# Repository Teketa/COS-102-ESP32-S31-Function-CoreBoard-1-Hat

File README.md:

# COS-102 hat for ESP32-S31-Function-CoreBoard-1

KiCad project for a hat that plugs onto the CoreBoard's J2 header and drives the
Delta COS-102 LED sign's IDC "IN" connector. It is built from `SCHEMATIC.md`, with
the GPIO map changed for the S31 board.

Files: `cos102_s31_hat.kicad_pro` / `.kicad_sch` / `.kicad_pcb`, plus a project
symbol library (`cos102_hat.kicad_sym`, the CoreBoard J2 symbol with real pin
names) and footprint library (`cos102_hat.pretty`, the button access hole).
Saved in KiCad 7 format, so KiCad 7, 8, 9 and 10 all open it (newer versions
upgrade it on save).

## GPIO map: firmware must change

The ESP32-S3 pins in `pins.h` (4-8, 15-18) are not on the S31 board's J2,
except GPIO4, and GPIO4 is also the Ethernet PHY interrupt (`ETH_INTN`, through
R83). The hat uses nine free pins next to each other on J2:

```c
#define PIN_CLK    47   // J2.13 -> U8A  -> R1  -> P1.10
#define PIN_R      48   // J2.14 -> U8D  -> R4  -> P1.4   (+ U10B -> R10 -> P1.1 copy)
#define PIN_G      45   // J2.15 -> U8C  -> R3  -> P1.3
#define PIN_B      46   // J2.16 -> U8B  -> R2  -> P1.2
#define PIN_LAT    43   // J2.17 -> U9A  -> R5  -> P1.9
#define PIN_GCLK   44   // J2.18 -> U9B  -> R6  -> P1.11
#define PIN_ADDR_A 40   // J2.19 -> U9C  -> R7  -> P1.8
#define PIN_ADDR_B 42   // J2.20 -> U9D  -> R8  -> P1.7
#define PIN_ADDR_C 39   // J2.21 -> U10A -> R9  -> P1.6
```

CLK and the three data lines share U8, as in `SCHEMATIC.md`.

Pins deliberately avoided, from the CoreBoard schematic and the ESP32-S31 IO guide:

| GPIO | Why |
|---|---|
| 4 | Also wired to the Ethernet PHY interrupt (ETH_INTN) through 0 Ohm R83 |
| 36, 37 | Strapping (VDD_SPI voltage, JTAG select) |
| 60 | Strapping + on-board RGB LED |
| 61 | Strapping (BOOT) + BOOT button |
| 58, 59 | UART0 to the CP2102N (console, `oc fast` etc.) |

Spare and free on J2: GPIO0-3, 20-25 (SD pins), 35, 38, 49.

## Power

Same as `SCHEMATIC.md`: J1 (display PSU 5 V) -> F1 2 A slow -> D1 TVS / C5 ->
FB1+FB2 -> L1 47 uH + C6 1000 uF -> FB3 -> buffers, and -> D2 SS34 -> C8 470 uF
-> CoreBoard 5V pins (J2.39/40).

On the CoreBoard, the 5V header pins are `VCC_5V`, the output of the LM66200
ideal-diode OR of both USB-C ports. That rail also feeds the 3.3 V buck, the
USB-A host switch (up to 500 mA) and the speaker amp. D2 stops the board's USB
from powering the panel. USB can stay plugged in for flashing.

GND_IN (J1 pin 2, D1, C5, FB2 pin 1) has its own copper island on the top layer
(`GND_IN_island` zone). The main GND pours on both layers start after FB2.

## Mechanics

- 65 x 55 mm, same outline as the CoreBoard. 3.5 mm corner radius, 4x M2.5 holes on the board's 58 x 48 mm grid.
- J2 is a 2x20 female socket (8.5 mm body) on the BOTTOM side. Every pad was
  checked against the CoreBoard header positions from Espressif's DXF; pin 1 is
  on the inner row at the left end.
- Stack height: 2.54 mm header plastic + 8.5 mm socket = 11 mm. Use M2.5 x 11 mm standoffs.
- Cut-out over the RJ45 (x >= 43.5 mm, y 17-44.5 mm). The CoreBoard's USB-A is
  a side-mount part standing on edge, so both are taller than 11 mm.
- 3.2 mm holes over the BOOT and RST buttons, so you can press them with a toothpick.
- Copper keep-out (both layers) along the left edge, where the module's PCB antenna hangs off the CoreBoard.
- `User.Drawings` shows the CoreBoard RJ45, USB-A and module outline for reference.

## Check before ordering

1. **P1 pin 1** against the ribbon's triangle mark (unchanged from `SCHEMATIC.md`).
2. **IDC pins 5, 13, 15** are left unconnected until they have been metered.
3. Panel 5 V current. Bench test with a current-limited supply first.

Already checked: ERC is clean (0 errors, 0 warnings) in your KiCad. The board
has no courtyard overlaps. J1's wire openings face the bottom board edge
(checked against its 3D model). J1 stands about 13.8 mm tall above the hat.

## Layout and routing

P1 (the ribbon to the panel) sits on the bottom edge next to J1, so both cables
plug in along the same edge. Pin 1 is at the left, in the same orientation as
before. The fuse F1 sits in the gap between P1 and J1. The input TVS/bypass/beads
(D1, C5, FB1, FB2) sit just above them. L1 and C6 are in the middle of the board.

The board is routed on 2 layers. Most tracks are on top. The bottom is a GND
plane, cut only by about 176 mm of short jumpers.

- 68 vias. Each buffer has a GND bus under its body that joins pins 1/4/7/10/13,
  with two vias to the plane. Each decoupling cap is tied straight to pins 13/14.
  Every other SMD GND pad has its own via.
- GND_IN (J1 pin 2, D1, C5, FB2 pin 1) is its own short 0.8 mm track and never touches the plane.
- Track widths: Power 0.8 mm, +5V_BUF 0.5 mm, panel side 0.3 mm, 3.3 V side 0.25 mm.
- Clock/data path lengths from J2 to P1: CLK 60 mm, G 53 mm, B 65 mm, R 74 mm
  (R includes the pin-1 copy branch). That's under 0.1 ns of skew, negligible at 18 MHz.
- DRC (zones filled): 0 unconnected, 0 clearance errors at 0.2 mm for signals and
  0.25 mm for power/GND. Left over: library silkscreen lines (P1's pin-1 marker,
  J1's front edge) that run past the board edge and get trimmed.

It was autorouted with a small grid router, because Freerouting isn't installed
here. Press B after any edit to refill the zones.

## JLCPCB (standard 2-layer, 1 oz) check

| Rule | JLCPCB minimum | This board |
|---|---|---|
| Track width / spacing | 0.10 / 0.10 mm | 0.25 / 0.20 mm |
| Via hole / diameter | 0.15 / 0.25 mm | 0.30 / 0.60 mm (power 0.40 / 0.80) |
| PTH annular ring | 0.18 mm (0.25 recommended) | 0.35 mm |
| Hole to hole, vias | 0.20 mm | 0.61 mm |
| Hole to hole, via to pad | 0.45 mm | 0.75 mm |
| Pad to pad | 0.15 mm | 0.20 mm |
| PTH hole to track | 0.28 mm | 0.55 mm |
| NPTH to copper | 0.20 mm | 0.25 mm |
| Copper to board edge | 0.20 mm | 0.50 mm |
| Solder mask bridge | 0.10 mm (green) | 0.67 mm (SOIC-14 pins) |
| Min NPTH | 0.50 mm | 3.2 mm |
| Silkscreen text height | 1.0 mm | 1.0 mm |
| Silkscreen line width | 0.15 mm | 0.12 mm in KiCad library footprints* |

\* KiCad's standard library footprints draw silkscreen outlines at 0.12 mm.
JLCPCB prints them, though possibly thinner or with small gaps. This is cosmetic
only and doesn't affect fabrication.

For JLCPCB assembly you would also need LCSC part numbers in the BOM. The
footprints are all standard. J1, P1, J2, C6 and C8 are through-hole parts, so
solder them by hand (or pay for THT assembly).

## BOM (JLCPCB / LCSC, checked against the JLCPCB catalogue of 2026-11-05)

`jlcpcb_bom.csv` is ready to upload to JLCPCB assembly. Every symbol and footprint also
carries an `LCSC` field, so the KiCad JLCPCB plugins pick the numbers up as well.

| Ref | Part | LCSC | Type | Stock | Price (1+) |
|---|---|---|---|---|---|
| U8, U9, U10 | TI SN74AHCT125DR, SOIC-14 | C155176 | Extended | 2,513 | $0.40 |
| R1-R10 | UNI-ROYAL 0603WAF330JT5E, 33 R 1 % 0603 | C23140 | Basic | 5.07 M | $0.0025 |
| C1-C3, C5, C7, C9 | YAGEO CC0603KRX7R9BB104, 100 nF 50 V X7R | C14663 | Basic | 50 M | $0.014 |
| C4 | Samsung CL21A106KAYNNNE, 10 uF 25 V X5R 0805 | C15850 | Basic | 3.7 M | $0.069 |
| L1 | Bourns SRR1260-470M, 47 uH, Isat 2.6 A, 86 mOhm | C1329363 | Extended | 600 | $1.48 |
| FB1, FB2 | Murata BLM31PG121SN1L, 1206, 3.5 A, 20 mOhm | C85841 | Extended | 49,437 | $0.16 |
| FB3 | Murata BLM18PG221SN1D, 0603, 1.4 A | C80165 | Extended | 298,012 | $0.015 |
| F1 | Littelfuse 0452002.MRL, 2 A slow-blow | C142852 | Extended | 12,284 | $0.33 |
| D1 | MDD SMBJ5.0A, unidirectional TVS | C113974 | Extended | 178,091 | $0.059 |
| D2 | MDD SS34, SMA | C8678 | Basic | 4.0 M | $0.035 |
| C6 (THT) | Rubycon 16YXF1000MEFC10X20, 1000 uF 16 V, 10x20, 78 mOhm | C110138 | Extended | 6,499 | $0.20 |
| C8 (THT) | Nichicon UHE1A471MPD1TD, 470 uF 10 V, 8 mm | C1579341 | Extended | 1,489 | $0.14 |
| J1 (THT) | Phoenix Contact 1729128 (MKDS 1,5/2-5,08) | C7509570 | Extended | 1,306 | $0.54 |
| P1 (THT) | XFCN BH254V-16P, 2x8 box header | C492443 | Extended | 114,323 | $0.16 |
| J2 (THT, bottom) | CONNFLY DS1023-2*20SF11, 2x20 female, 8.5 mm | C132132 | Extended | 2,884 | $0.49 |
| H1-H4 | M2.5 mounting holes, no part | | | | |

- SMT parts cost about $3.60 per board. Six SMT parts are Extended (U, L1, FB1/2, FB3, F1, D1),
  which adds about $18 in setup fees per order ($3 per unique Extended part).
  None of them has a Basic equivalent in the catalogue.
- The through-hole parts (C6, C8, J1, P1, J2) cost about $1.50. Solder them by hand, or
  pay for JLCPCB's THT assembly. J2 goes on the bottom side.
- Lowest stock is L1 (600). Stock moves, so re-check before ordering.
- Cheaper J1 alternative: KF128-5.08-2P-AA (C474952, $0.19, 62k in stock), same 5.08 mm
  pitch. Check its pin and body against the MKDS footprint before swapping.
- The parts file (CPL) and Gerbers are best produced with the JLCPCB fabrication
  plugin in KiCad, which applies JLCPCB's rotation offsets per footprint.

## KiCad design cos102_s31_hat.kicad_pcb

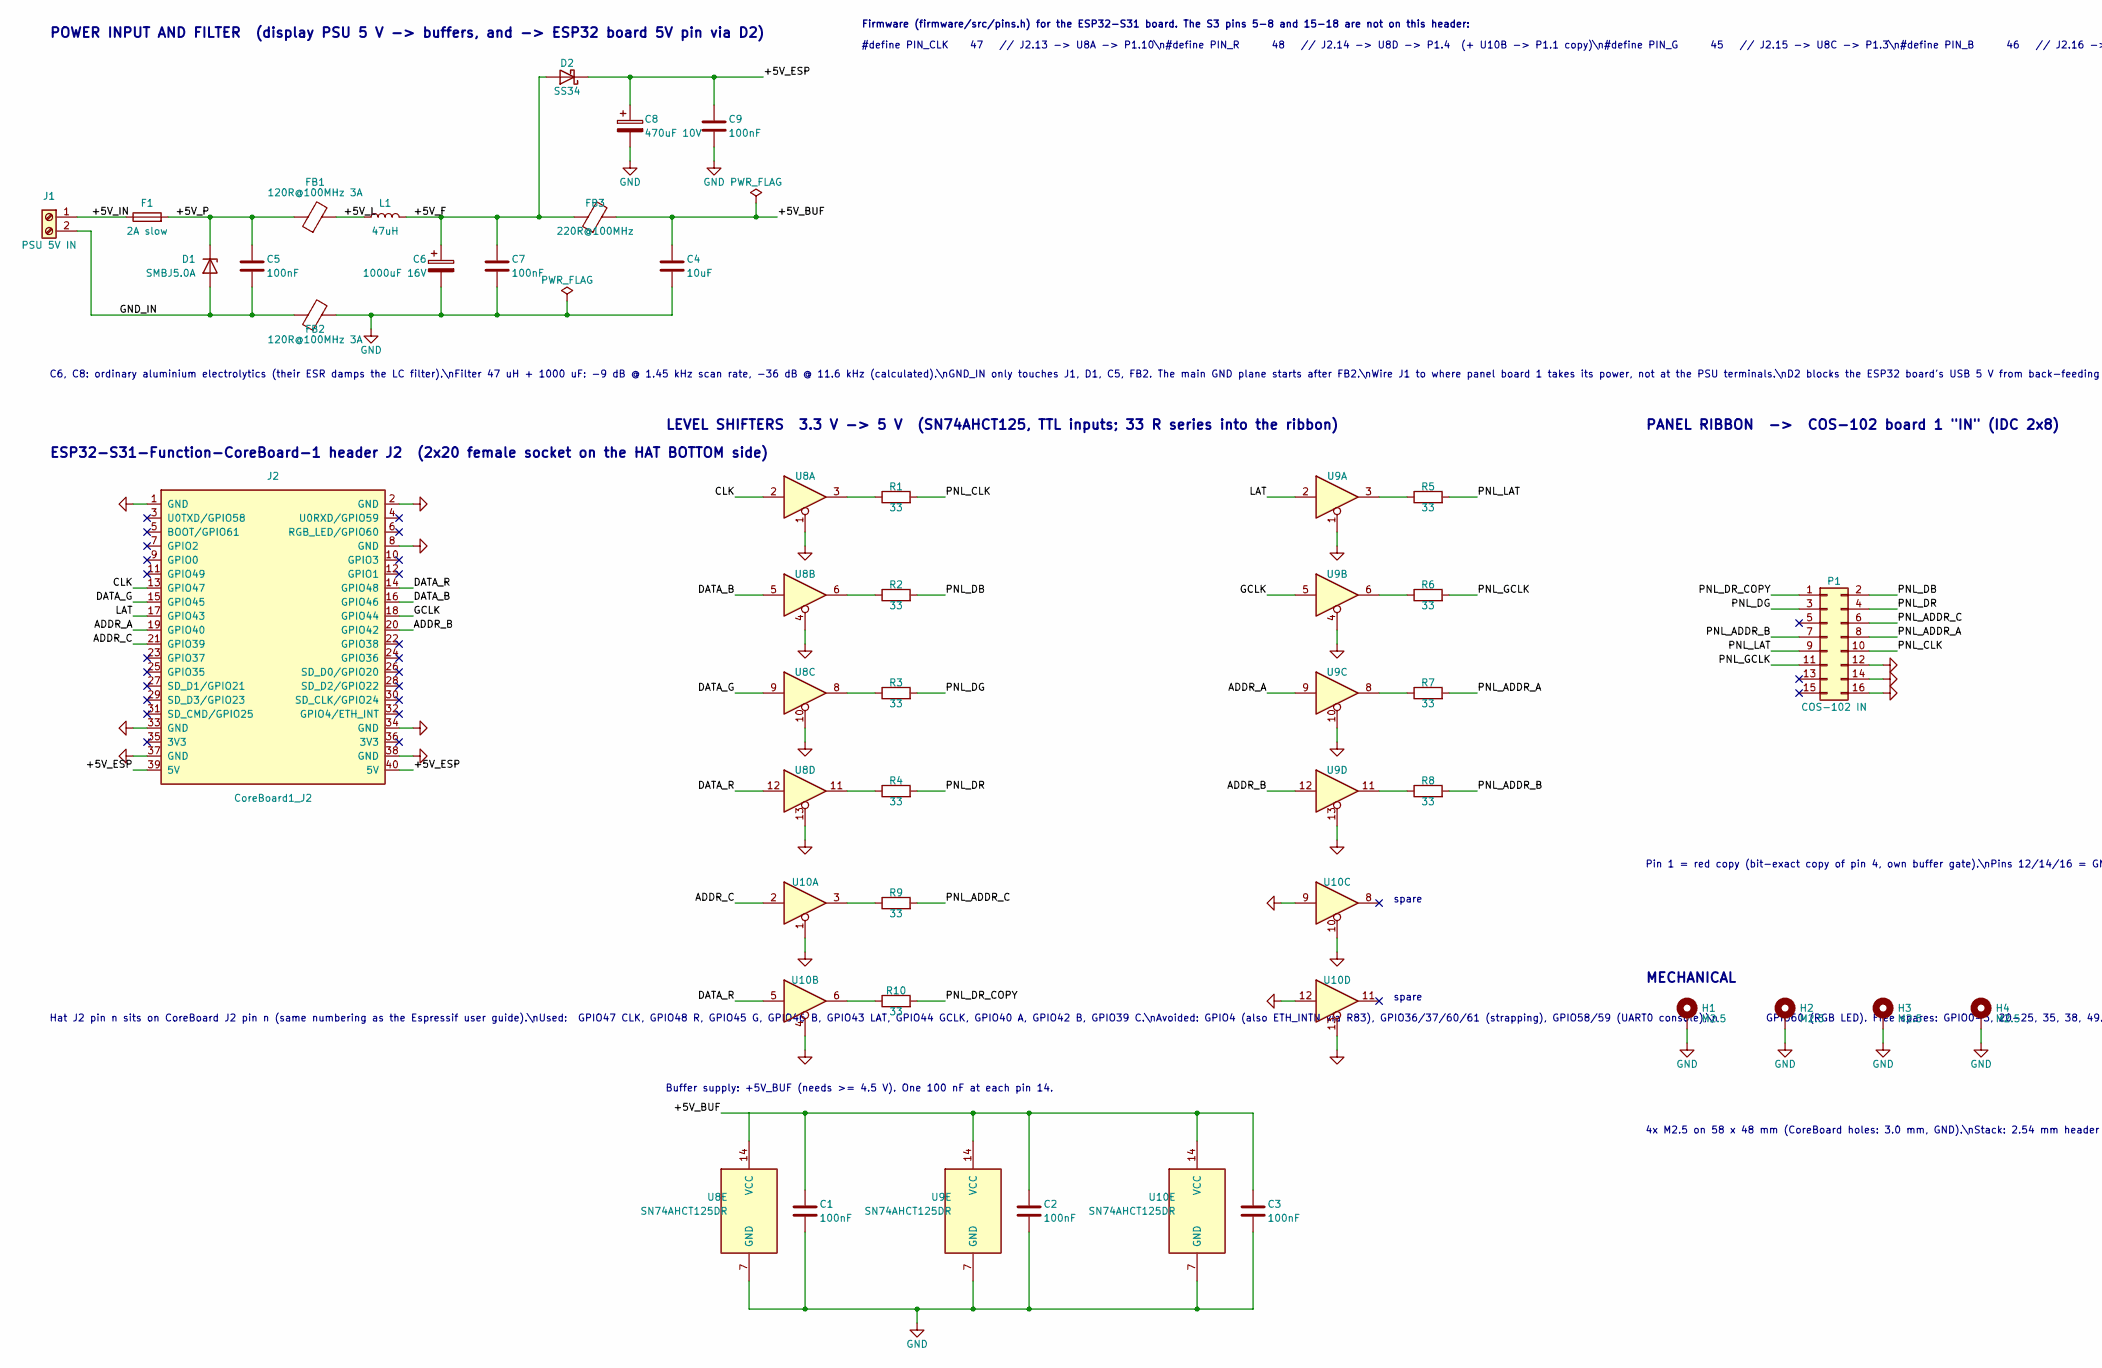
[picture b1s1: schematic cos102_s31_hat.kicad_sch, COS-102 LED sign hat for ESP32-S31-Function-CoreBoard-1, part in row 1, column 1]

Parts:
C1, C2, C3, C7, C9: 100nF; C_0603_1608Metric; MPN YAGEO CC0603KRX7R9BB104 (100nF 50V X7R); LCSC C14663
C4: 10uF; C_0805_2012Metric; Voltage 10V X5R; MPN Samsung CL21A106KAYNNNE (10uF 25V X5R); LCSC C15850
C5: 100nF; C_0603_1608Metric; Voltage 16V X7R; MPN YAGEO CC0603KRX7R9BB104 (100nF 50V X7R); LCSC C14663
C6: 1000uF 16V; CP_Radial_D10.0mm_P5.00mm; MPN Rubycon 16YXF1000MEFC10X20 (1000uF 16V,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; LCSC C110138
C8: 470uF 10V; CP_Radial_D8.0mm_P3.50mm; MPN Nichicon UHE1A471MPD1TD (470uF 10V, 8 m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; LCSC C1579341
D1: SMBJ5.0A; D_SMB; MPN MDD SMBJ5.0A (unidirectional TVS, SMB); LCSC C113974
D2: SS34; D_SMA; MPN MDD SS34 (3 A 40 V Schottky, SMA); LCSC C8678
F1: 2A slow; Fuse_Littelfuse-NANO2-451_453; MPN Littelfuse 0452002.MRL (2 A slow-blow, 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; LCSC C142852
FB1, FB2: 120R@100MHz 3A; L_1206_3216Metric; MPN Murata BLM31PG121SN1L (120R@100MHz, 3.5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; LCSC C85841
FB3: 220R@100MHz; L_0603_1608Metric; MPN Murata BLM18PG221SN1D (220R@100MHz, 1.4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; LCSC C80165
H1, H2, H3, H4: M2.5; MountingHole_2.7mm_M2.5_Pad_Via
J1: PSU 5V IN; TerminalBlock_Phoenix_MKDS-1,5-2-5.08_1x02_P5.08mm_Horizont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; MPN Phoenix Contact 1729128 (MKDS 1,5/2-5,0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; LCSC C7509570
J2: CoreBoard1_J2; PinSocket_2x20_P2.54mm_Vertical; MPN CONNFLY DS1023-2*20SF11 (2x20 female 2.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; LCSC C132132
L1: 47uH; L_Bourns_SRR1260; MPN Bourns SRR1260-470M (47uH, Isat 2.6 A, 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; LCSC C1329363
P1: COS-102 IN; IDC-Header_2x08_P2.54mm_Vertical; MPN XFCN BH254V-16P (2x8 box header 2.54 mm); LCSC C492443
R1, R2, R3, R4, R5, R6, R7, R8, R9, R10: 33; R_0603_1608Metric; MPN UNI-ROYAL 0603WAF330JT5E (33R 1%); LCSC C23140
U8, U9, U10: SN74AHCT125DR; SOIC-14_3.9x8.7mm_P1.27mm; MPN TI SN74AHCT125DR; LCSC C155176

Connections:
+5V_BUF: C1.1, C2.1, C3.1, C4.1, FB3.2, U8.14 (VCC), U9.14 (VCC), U10.14 (VCC)
+5V_ESP: C8.1, C9.1, D2.1 (K), J2.39 (5V), J2.40 (5V)
+5V_F: C6.1, C7.1, D2.2 (A), FB3.1, L1.2
+5V_IN: F1.1, J1.1
+5V_L: FB1.2, L1.1
+5V_P: C5.1, D1.1 (K), F1.2, FB1.1
ADDR_A: J2.19 (GPIO40), U9.9
ADDR_B: J2.20 (GPIO42), U9.12
ADDR_C: J2.21 (GPIO39), U10.2
CLK: J2.13 (GPIO47), U8.2
DATA_B: J2.16 (GPIO46), U8.5
DATA_G: J2.15 (GPIO45), U8.9
DATA_R: J2.14 (GPIO48), U8.12, U10.5
GCLK: J2.18 (GPIO44), U9.5
GND: C1.2, C2.2, C3.2, C4.2, C6.2, C7.2, C8.2, C9.2, FB2.2, H1.1, H2.1, H3.1, H4.1, J2.1 (GND), J2.2 (GND), J2.8 (GND), J2.33 (GND), J2.34 (GND), J2.37 (GND), J2.38 (GND), P1.12, P1.14, P1.16, U8.1, U8.4, U8.7 (GND), U8.10, U8.13, U9.1, U9.4, U9.7 (GND), U9.10, U9.13, U10.1, U10.4, U10.7 (GND), U10.9, U10.10, U10.12, U10.13
GND_IN: C5.2, D1.2 (A), FB2.1, J1.2
LAT: J2.17 (GPIO43), U9.2
unnamed: R1.1, U8.3
unnamed: R2.1, U8.6
unnamed: R3.1, U8.8
unnamed: R4.1, U8.11
unnamed: R5.1, U9.3
unnamed: R6.1, U9.6
unnamed: R7.1, U9.8
unnamed: R8.1, U9.11
unnamed: R9.1, U10.3
unnamed: R10.1, U10.6
PNL_ADDR_A: P1.8, R7.2
PNL_ADDR_B: P1.7, R8.2
PNL_ADDR_C: P1.6, R9.2
PNL_CLK: P1.10, R1.2
PNL_DB: P1.2, R2.2
PNL_DG: P1.3, R3.2
PNL_DR: P1.4, R4.2
PNL_DR_COPY: P1.1, R10.2
PNL_GCLK: P1.11, R6.2
PNL_LAT: P1.9, R5.2

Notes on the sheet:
POWER INPUT AND FILTER (display PSU 5 V -> buffers, and -> ESP32 board 5V pin via D2)
C6, C8: ordinary aluminium electrolytics (their ESR damps the LC filter).\nFilter 47 uH + 1000 uF: -9 dB @ 1.45 kHz scan rate, -36 dB @ 11.6 kHz (calculated).\nGND_IN only touches J1, D1, C5, FB2. The main GND plane starts after FB2.\nWire J1 to where panel board 1 takes its power, not at the PSU t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
ESP32-S31-Function-CoreBoard-1 header J2 (2x20 female socket on the HAT BOTTOM side)
Hat J2 pin n sits on CoreBoard J2 pin n (same numbering as the Espressif user guide).\nUsed: GPIO47 CLK, GPIO48 R, GPIO45 G, GPIO46 B, GPIO43 LAT, GPIO44 GCLK, GPIO40 A, GPIO42 B, GPIO39 C.\nAvoided: GPIO4 (also ETH_INTN via R83), GPIO36/37/60/61 (strapping), GPIO58/59 (UART0 console),\n GPIO60 (RG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
LEVEL SHIFTERS 3.3 V -> 5 V (SN74AHCT125, TTL inputs; 33 R series into the ribbon)
spare
Buffer supply: +5V_BUF (needs >= 4.5 V). One 100 nF at each pin 14.
PANEL RIBBON -> COS-102 board 1 "IN" (IDC 2x8)
Pin 1 = red copy (bit-exact copy of pin 4, own buffer gate).\nPins 12/14/16 = GND (measured).\nPins 5/13/15 unknown: NOT connected until metered.\nPanel inputs: 5 V HC logic (SN74HC244 buffers).\nStable to ~19.5 MHz; 18 MHz recommended.
MECHANICAL
4x M2.5 on 58 x 48 mm (CoreBoard holes: 3.0 mm, GND).\nStack: 2.54 mm header plastic + 8.5 mm socket = 11 mm.\nUse M2.5 x 11 mm standoffs.\nCut-out over the RJ45 and side-mount USB-A (13+ mm tall).\n3.2 mm holes give access to BOOT and RST.\nNo copper over the module antenna (left edge).
Firmware (firmware/src/pins.h) for the ESP32-S31 board. The S3 pins 5-8 and 15-18 are not on this header:
#define PIN_CLK 47 // J2.13 -> U8A -> P1.10\n#define PIN_R 48 // J2.14 -> U8D -> P1.4 (+ U10B -> P1.1 copy)\n#define PIN_G 45 // J2.15 -> U8C -> P1.3\n#define PIN_B 46 // J2.16 -> U8B -> P1.2\n#define PIN_LAT 43 // J2.17 -> U9A -> P1.9\n#define PIN_GCLK 44 // J2.18 -> U9B -> P1.11\n#define PIN_ADDR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

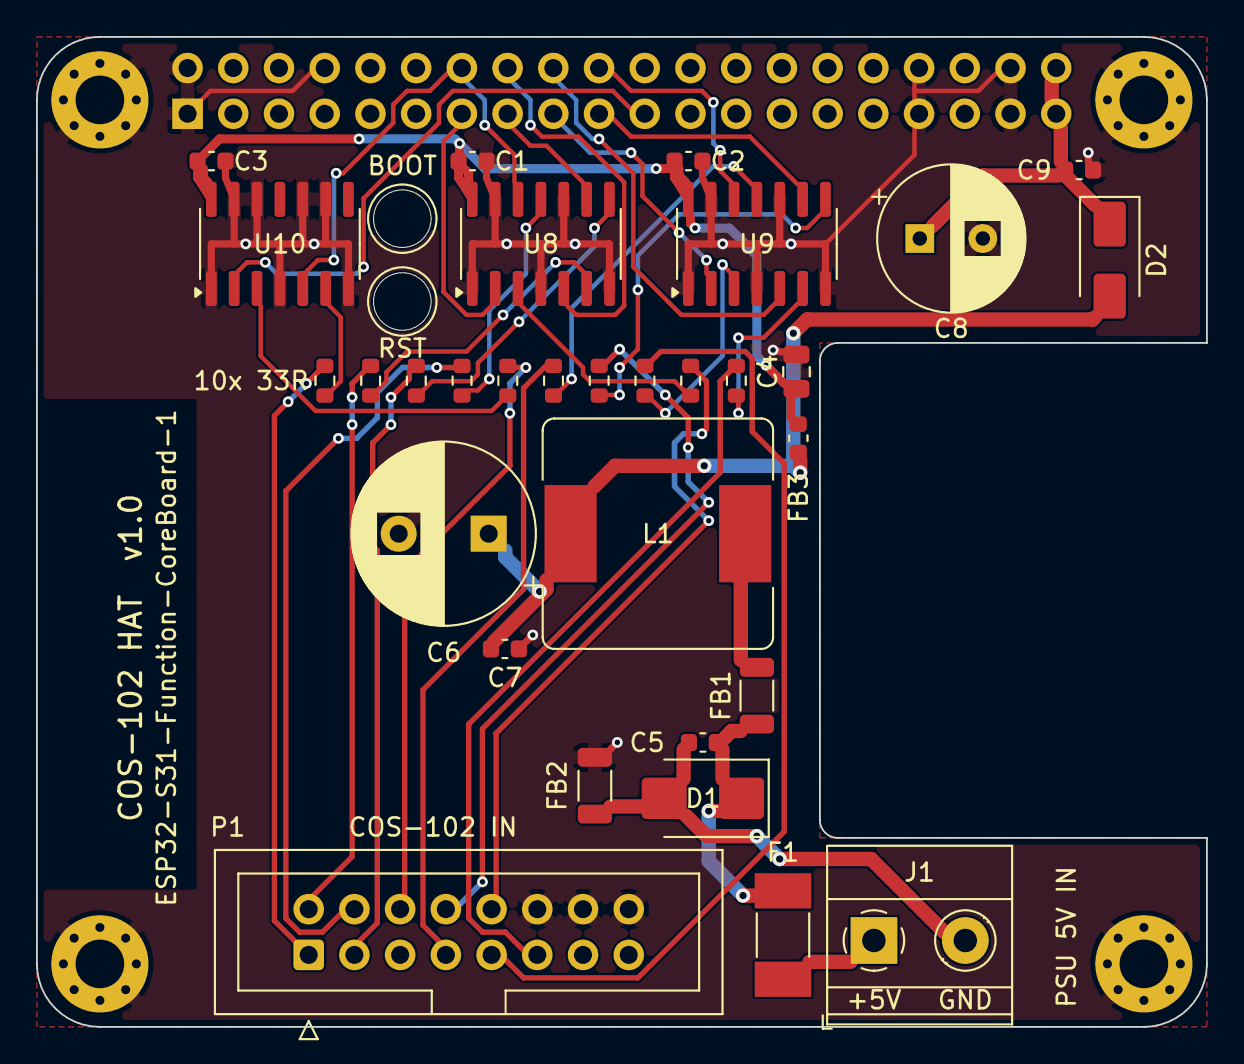
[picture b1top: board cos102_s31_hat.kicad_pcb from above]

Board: 2 copper layers, 65.0 x 55.0 mm, 38 parts (1 on the bottom side), 37 nets.

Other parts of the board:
H5: BOOT access; AccessHole_3.2mm
H6: RST access; AccessHole_3.2mm

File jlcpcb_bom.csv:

Comment,Designator,Footprint,LCSC,Assembly
100nF,"C1,C2,C3,C5,C7,C9",C_0603_1608Metric,C14663,SMT
10uF,C4,C_0805_2012Metric,C15850,SMT
1000uF 16V,C6,CP_Radial_D10.0mm_P5.00mm,C110138,THT (hand solder)
470uF 10V,C8,CP_Radial_D8.0mm_P3.50mm,C1579341,THT (hand solder)
SMBJ5.0A,D1,D_SMB,C113974,SMT
SS34,D2,D_SMA,C8678,SMT
2A slow,F1,Fuse_Littelfuse-NANO2-451_453,C142852,SMT
120R@100MHz 3A,"FB1,FB2",L_1206_3216Metric,C85841,SMT
220R@100MHz,FB3,L_0603_1608Metric,C80165,SMT
PSU 5V IN,J1,"TerminalBlock_Phoenix_MKDS-1,5-2-5.08_1x02_P5.08mm_Horizontal",C7509570,THT (hand solder)
CoreBoard1_J2,J2,PinSocket_2x20_P2.54mm_Vertical,C132132,THT (hand solder)
47uH,L1,L_Bourns_SRR1260,C1329363,SMT
COS-102 IN,P1,IDC-Header_2x08_P2.54mm_Vertical,C492443,THT (hand solder)
33,"R1,R2,R3,R4,R5,R6,R7,R8,R9,R10",R_0603_1608Metric,C23140,SMT
SN74AHCT125DR,"U8,U9,U10",SOIC-14_3.9x8.7mm_P1.27mm,C155176,SMT
